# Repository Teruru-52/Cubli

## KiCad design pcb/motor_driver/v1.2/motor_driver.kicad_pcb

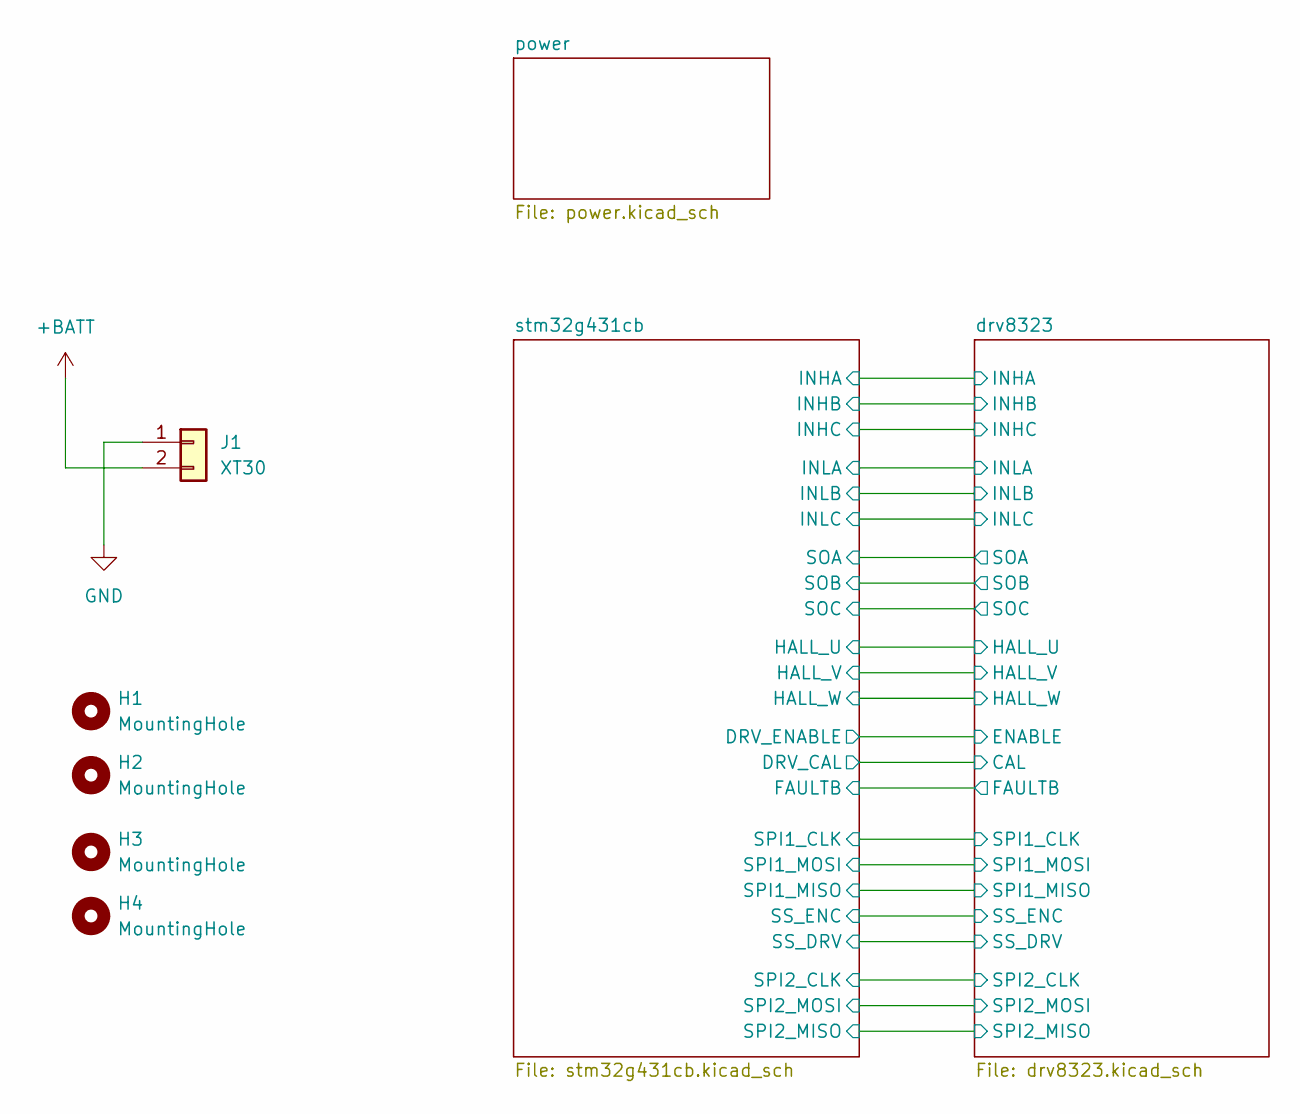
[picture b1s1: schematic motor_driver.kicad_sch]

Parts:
H1, H2, H3, H4: MountingHole; MountingHole_3.2mm_M3_Pad_TopBottom
J1: XT30; AMASS_XT30U-F_1x02_P5.0mm_Vertical

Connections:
+BATT: J1.2; also elsewhere on the board
GND: J1.1; also elsewhere on the board

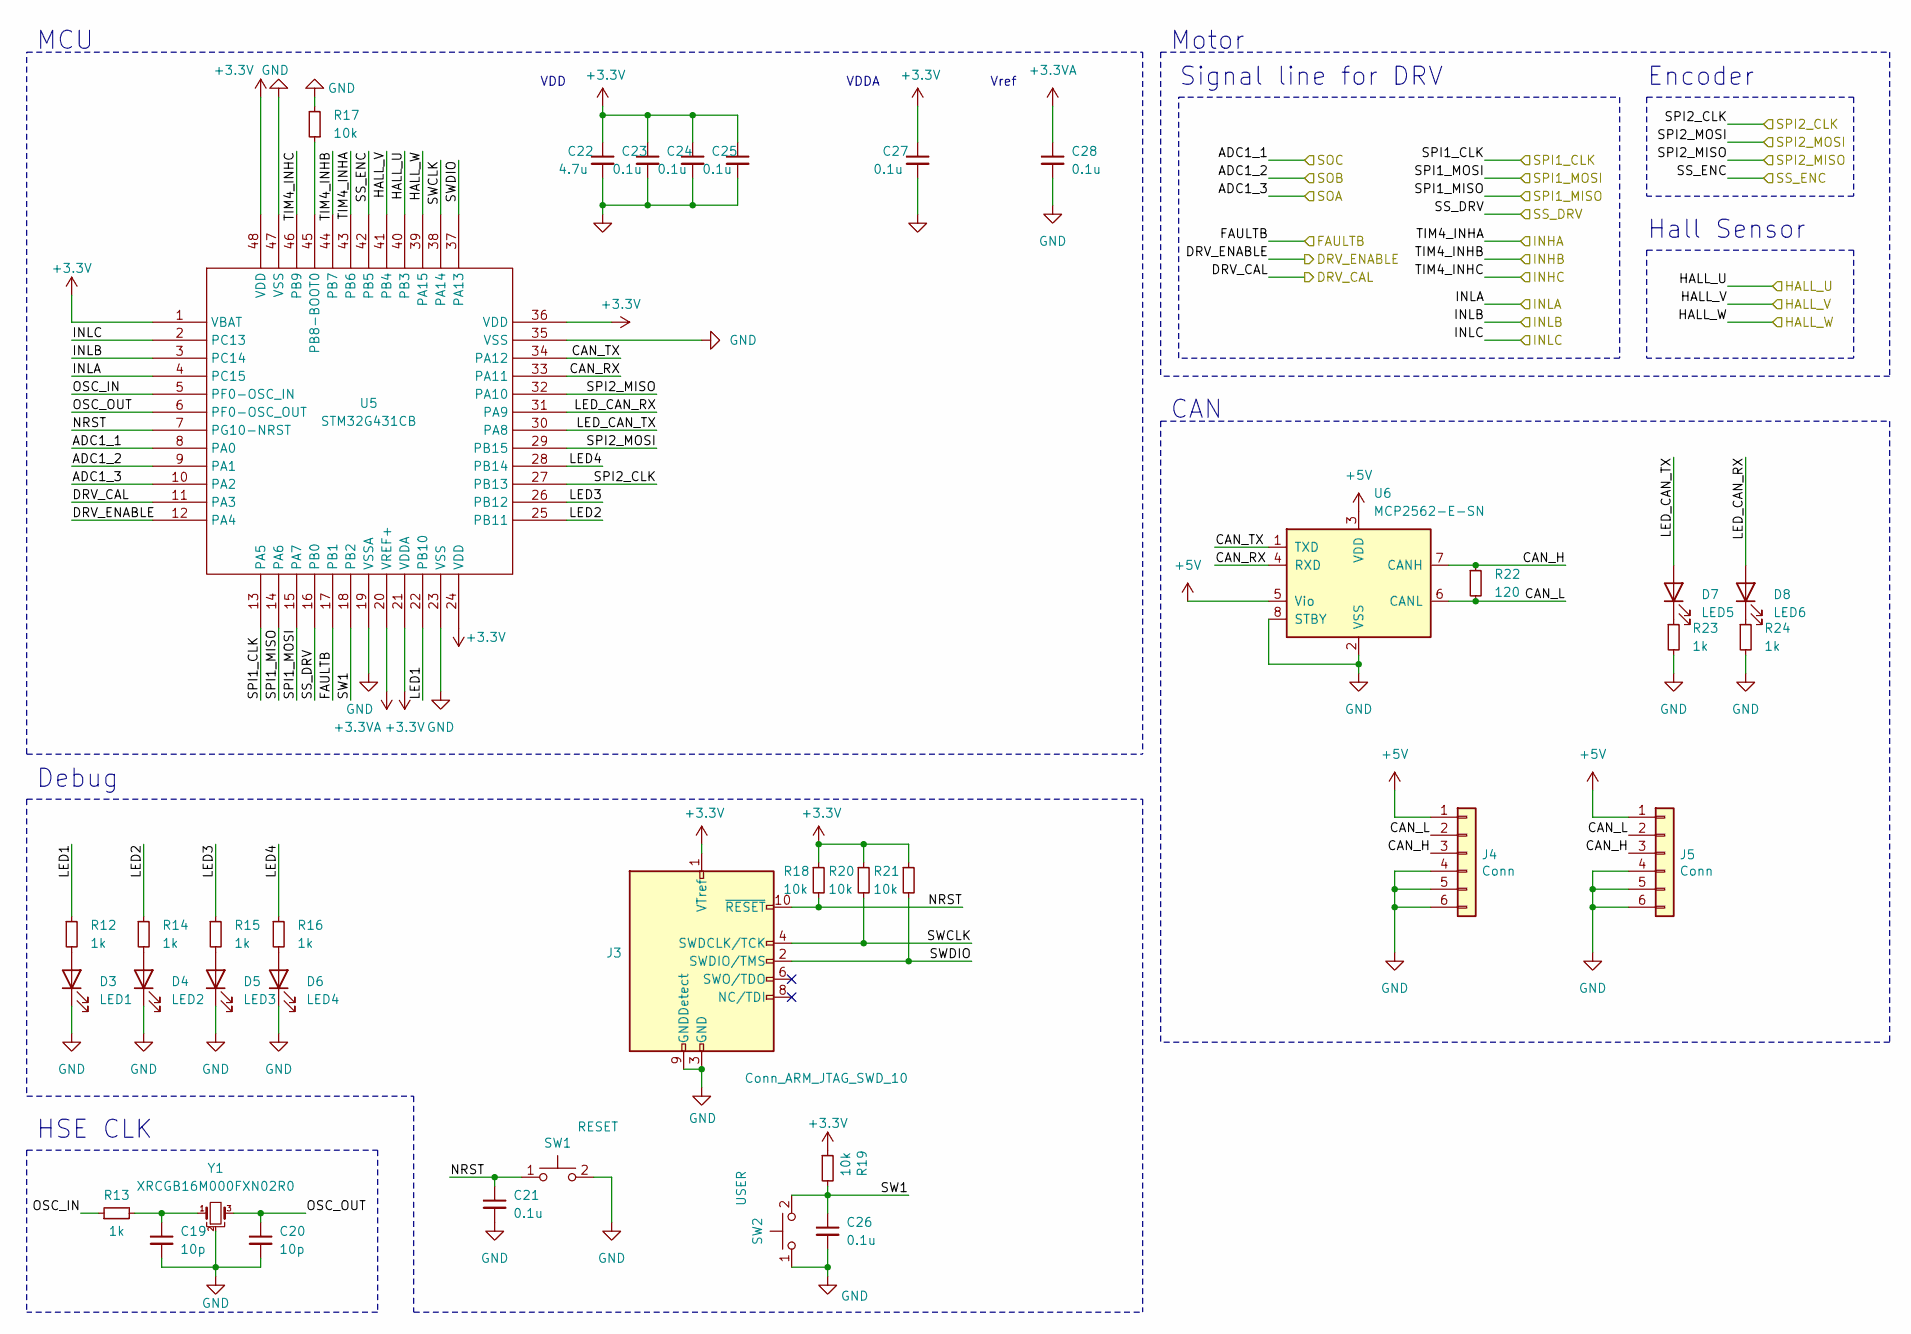
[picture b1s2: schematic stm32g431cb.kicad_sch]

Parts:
C19, C20: 10p; C_0402_1005Metric_Pad0.74x0.62mm_HandSolder
C21, C26: 0.1u; C_0603_1608Metric_Pad1.08x0.95mm_HandSolder
C22: 4.7u; C_0603_1608Metric
C23, C24, C25, C27, C28: 0.1u; C_0603_1608Metric
D3: LED1; LED_0603_1608Metric
D4: LED2; LED_0603_1608Metric
D5: LED3; LED_0603_1608Metric
D6: LED4; LED_0603_1608Metric
D7: LED5; LED_0603_1608Metric
D8: LED6; LED_0603_1608Metric
J3: Conn_ARM_JTAG_SWD_10; 322110010000
J4, J5: Conn; 21322604YY
R12, R14, R15, R16, R23, R24: 1k; R_0603_1608Metric_Pad0.98x0.95mm_HandSolder
R13: 1k; R_0402_1005Metric_Pad0.72x0.64mm_HandSolder
R17, R18, R19, R20, R21: 10k; R_0603_1608Metric_Pad0.98x0.95mm_HandSolder
R22: 120; R_0603_1608Metric_Pad0.98x0.95mm_HandSolder
SW1: RESET; TVAF06-A020B-R
SW2: USER; TVAF06-A020B-R
U5: STM32G431CB; LQFP-48_7x7mm_P0.5mm
U6: MCP2562-E-SN; SOIC-8_3.9x4.9mm_P1.27mm
Y1: XRCGB16M000FXN02R0

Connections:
+3.3V: C22.1, C23.1, C24.1, C25.1, C27.1, J3.1 (VTref), R18.1, R19.1, R20.1, R21.1, U5.1 (VBAT), U5.21 (VDDA), U5.24 (VDD), U5.36 (VDD), U5.48 (VDD); also elsewhere on the board
+3.3VA: C28.1, U5.20 (VREF+); also elsewhere on the board
+5V: J4.1, J5.1, U6.3 (VDD), U6.5 (Vio); also elsewhere on the board
/drv8323/HALL_U: U5.40 (PB3); also elsewhere on the board
/drv8323/HALL_V: U5.41 (PB4); also elsewhere on the board
/drv8323/HALL_W: U5.39 (PA15); also elsewhere on the board
/drv8323/SPI1_CLK: U5.13 (PA5); also elsewhere on the board
/drv8323/SPI1_MISO: U5.14 (PA6); also elsewhere on the board
/drv8323/SPI1_MOSI: U5.15 (PA7); also elsewhere on the board
/drv8323/SPI2_CLK: U5.27 (PB13); also elsewhere on the board
/drv8323/SPI2_MISO: U5.32 (PA10); also elsewhere on the board
/drv8323/SPI2_MOSI: U5.29 (PB15); also elsewhere on the board
/drv8323/SS_ENC: U5.42 (PB5); also elsewhere on the board
/stm32g431cb/ADC1_1: U5.8 (PA0); also elsewhere on the board
/stm32g431cb/ADC1_2: U5.9 (PA1); also elsewhere on the board
/stm32g431cb/ADC1_3: U5.10 (PA2); also elsewhere on the board
/stm32g431cb/CAN_H: J4.3, J5.3, R22.1, U6.7 (CANH)
/stm32g431cb/CAN_L: J4.2, J5.2, R22.2, U6.6 (CANL)
/stm32g431cb/CAN_RX: U5.33 (PA11), U6.4 (RXD)
/stm32g431cb/CAN_TX: U5.34 (PA12), U6.1 (TXD)
/stm32g431cb/DRV_CAL: U5.11 (PA3); also elsewhere on the board
/stm32g431cb/DRV_ENABLE: U5.12 (PA4); also elsewhere on the board
/stm32g431cb/FAULTB: U5.17 (PB1); also elsewhere on the board
/stm32g431cb/INLA: U5.4 (PC15); also elsewhere on the board
/stm32g431cb/INLB: U5.3 (PC14); also elsewhere on the board
/stm32g431cb/INLC: U5.2 (PC13); also elsewhere on the board
/stm32g431cb/LED1: R12.1, U5.22 (PB10)
/stm32g431cb/LED2: R14.1, U5.25 (PB11)
/stm32g431cb/LED3: R15.1, U5.26 (PB12)
/stm32g431cb/LED4: R16.1, U5.28 (PB14)
/stm32g431cb/LED_CAN_RX: D8.2 (A), U5.31 (PA9)
/stm32g431cb/LED_CAN_TX: D7.2 (A), U5.30 (PA8)
/stm32g431cb/NRST: C21.1, J3.10 (~RESET), R18.2, SW1.1, U5.7 (PG10-NRST)
/stm32g431cb/OSC_IN: R13.1, U5.5 (PF0-OSC_IN)
/stm32g431cb/OSC_OUT: C20.1, U5.6 (PF0-OSC_OUT), Y1.3
/stm32g431cb/SS_DRV: U5.16 (PB0); also elsewhere on the board
/stm32g431cb/SW1: C26.1, R19.2, SW2.2, U5.18 (PB2)
/stm32g431cb/SWCLK: J3.4 (SWDCLK/TCK), R20.2, U5.38 (PA14)
/stm32g431cb/SWDIO: J3.2 (SWDIO/TMS), R21.2, U5.37 (PA13)
/stm32g431cb/TIM4_INHA: U5.43 (PB6); also elsewhere on the board
/stm32g431cb/TIM4_INHB: U5.44 (PB7); also elsewhere on the board
/stm32g431cb/TIM4_INHC: U5.46 (PB9); also elsewhere on the board
GND: C19.2, C20.2, C21.2, C22.2, C23.2, C24.2, C25.2, C26.2, C27.2, C28.2, D3.1 (K), D4.1 (K), D5.1 (K), D6.1 (K), J3.3 (GND), J3.5 (GND), J3.9 (GNDDetect), J4.4, J4.5, J4.6, J5.4, J5.5, J5.6, R17.2, R23.2, R24.2, SW1.2, SW2.1, U5.19 (VSSA), U5.23 (VSS), U5.35 (VSS), U5.47 (VSS), U6.2 (VSS), U6.8 (STBY), Y1.2; also elsewhere on the board
unnamed: C19.1, R13.2, Y1.1
unnamed: D3.2 (A), R12.2
unnamed: D4.2 (A), R14.2
unnamed: D5.2 (A), R15.2
unnamed: D6.2 (A), R16.2
unnamed: D7.1 (K), R23.1
unnamed: D8.1 (K), R24.1
unnamed: R17.1, U5.45 (PB8-BOOT0)

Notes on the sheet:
Motor
HSE CLK
MCU
CAN
Encoder
Signal line for DRV
Debug
VDD
Vref
VDDA
Hall Sensor

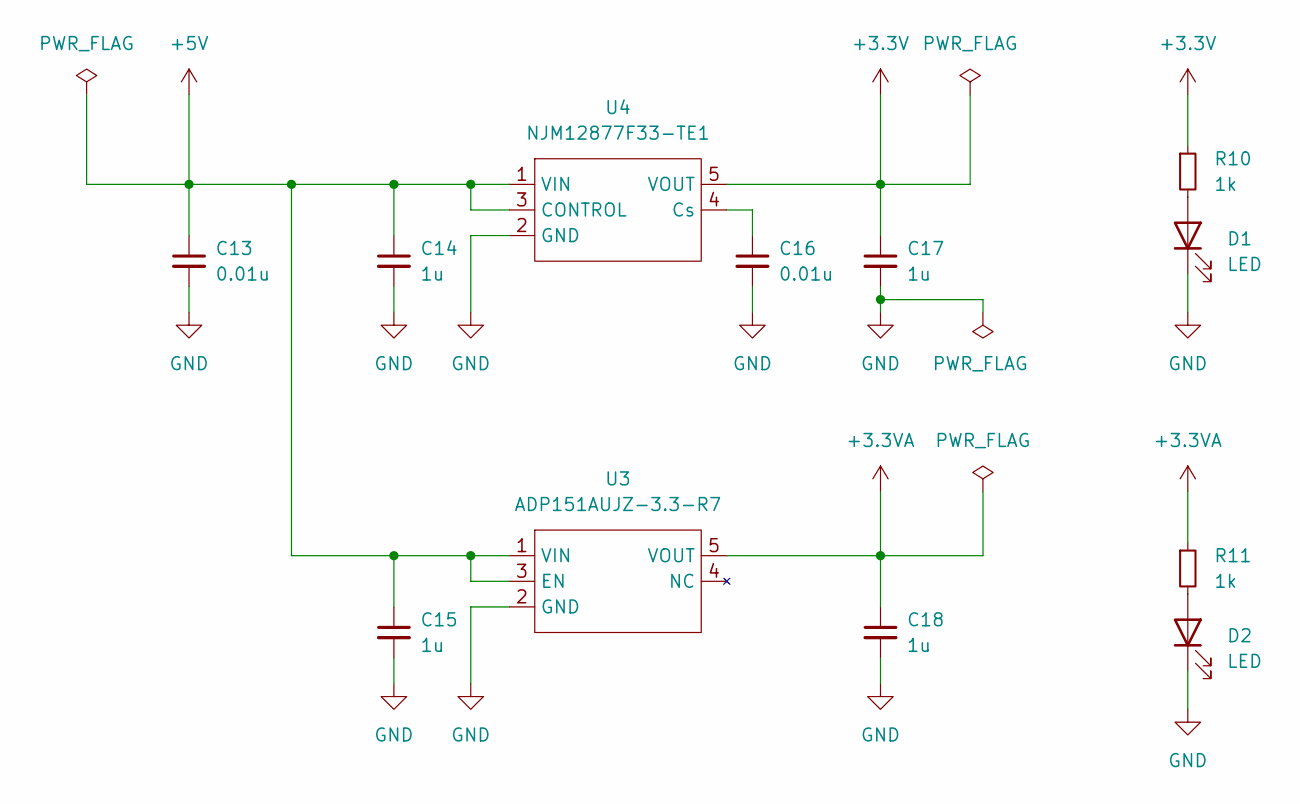
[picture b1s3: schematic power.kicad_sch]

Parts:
C13, C16: 0.01u; C_0603_1608Metric_Pad1.08x0.95mm_HandSolder
C14, C15, C17, C18: 1u; C_0603_1608Metric_Pad1.08x0.95mm_HandSolder
D1, D2: LED; LED_0603_1608Metric
R10, R11: 1k; R_0603_1608Metric_Pad0.98x0.95mm_HandSolder
U3: ADP151AUJZ-3.3-R7; SOT-23-5_HandSoldering
U4: NJM12877F33-TE1; SOT-23-5_HandSoldering

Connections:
+3.3V: C17.1, R10.1, U4.5 (VOUT); also elsewhere on the board
+3.3VA: C18.1, R11.1, U3.5 (VOUT); also elsewhere on the board
+5V: C13.1, C14.1, C15.1, U3.1 (VIN), U3.3 (EN), U4.1 (VIN), U4.3 (CONTROL); also elsewhere on the board
GND: C13.2, C14.2, C15.2, C16.2, C17.2, C18.2, D1.1 (K), D2.1 (K), U3.2 (GND), U4.2 (GND); also elsewhere on the board
unnamed: D1.2 (A), R10.2
unnamed: D2.2 (A), R11.2
unnamed: C16.1, U4.4 (Cs)

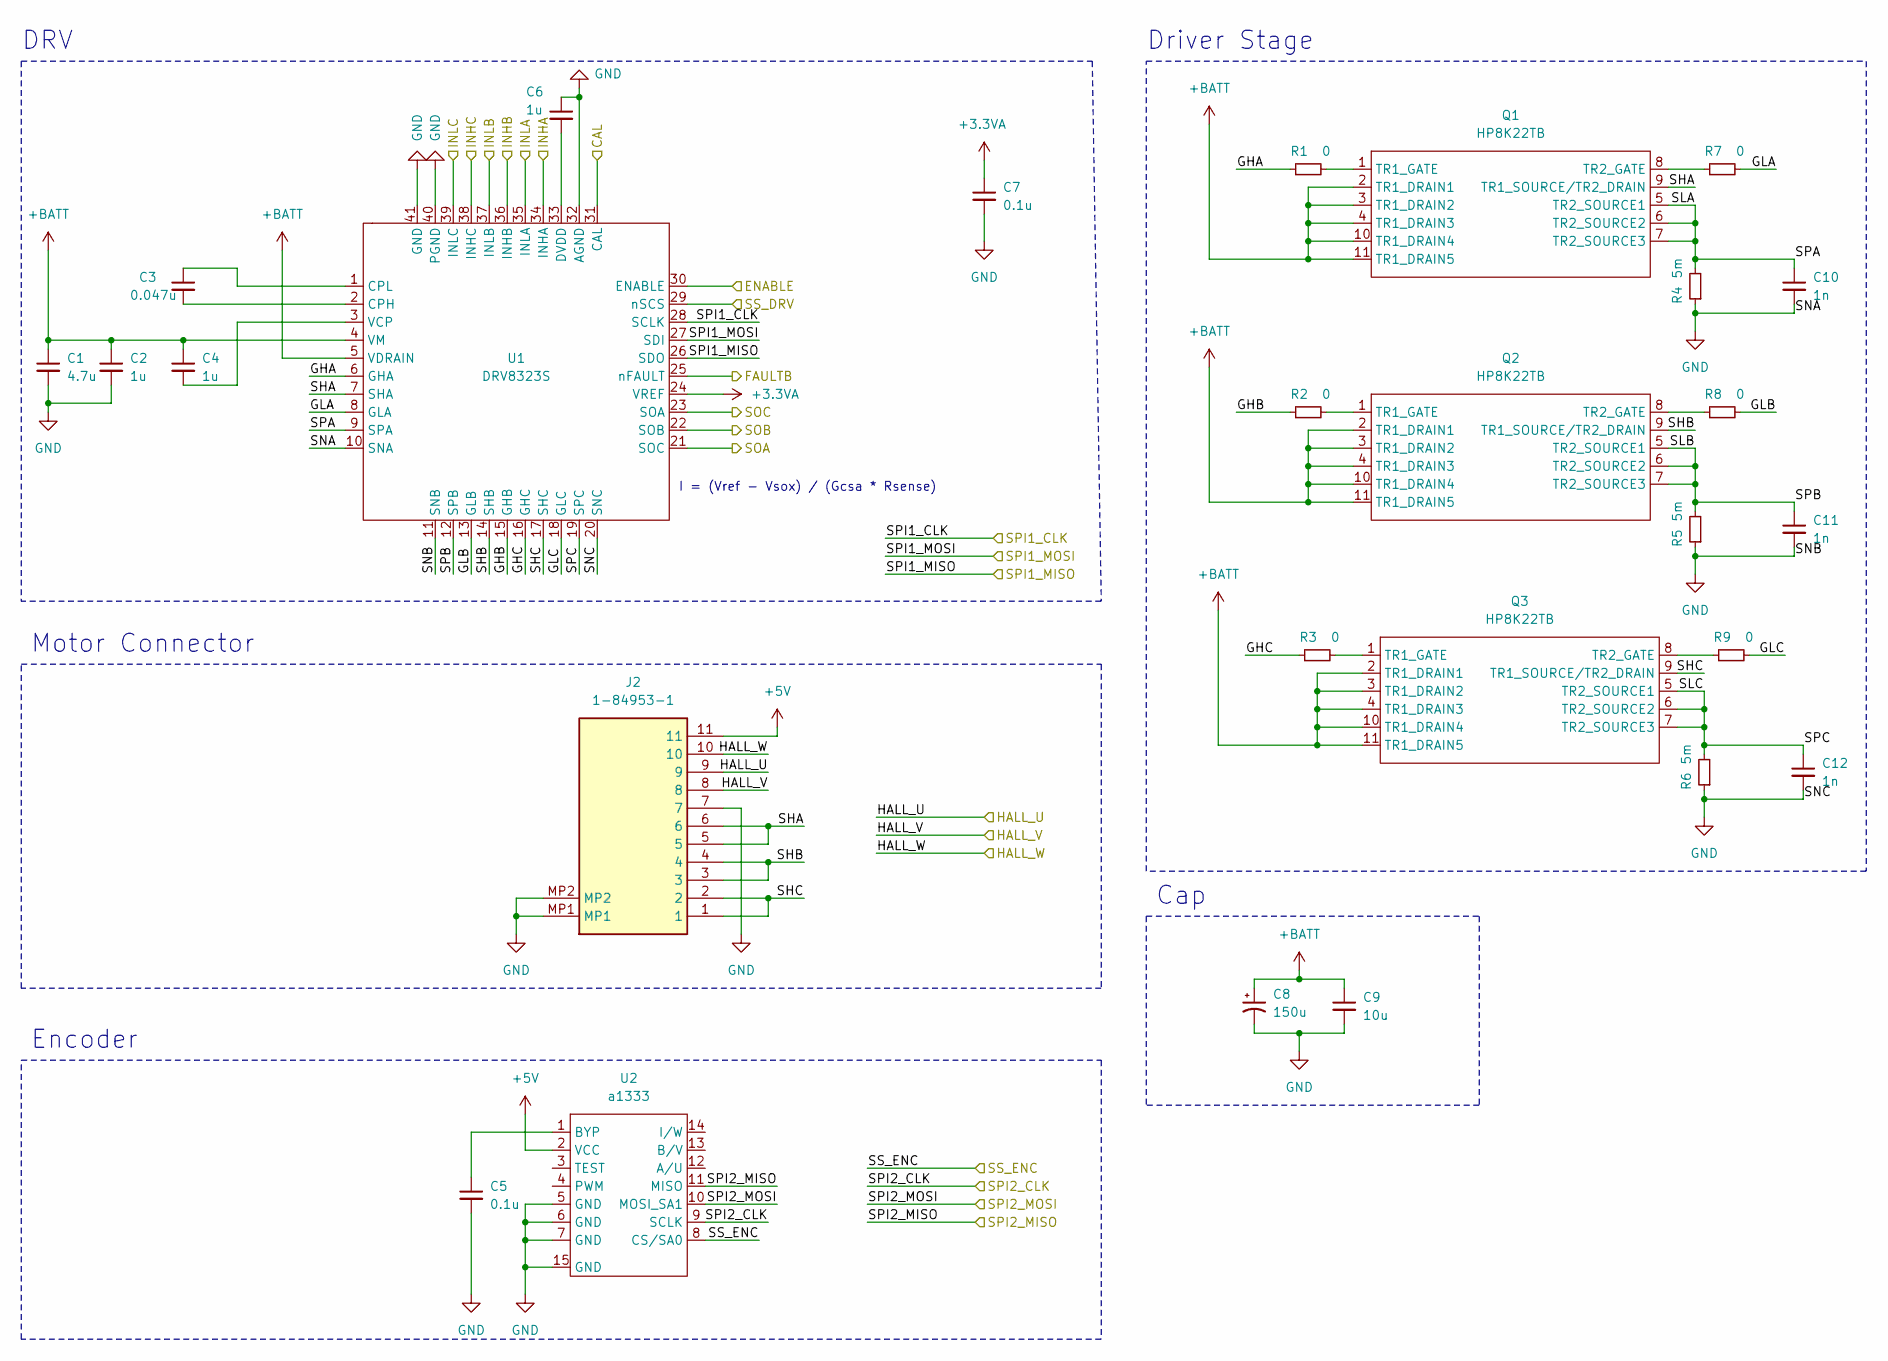
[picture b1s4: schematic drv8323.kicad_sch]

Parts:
C1: 4.7u; C_0603_1608Metric_Pad1.08x0.95mm_HandSolder
C2, C4, C6: 1u; C_0603_1608Metric_Pad1.08x0.95mm_HandSolder
C3: 0.047u; C_0603_1608Metric_Pad1.08x0.95mm_HandSolder
C5: 0.1u; C_0603_1608Metric_Pad1.08x0.95mm_HandSolder
C7: 0.1u; C_0402_1005Metric_Pad0.74x0.62mm_HandSolder
C8: 150u; CP_Elec_6.3x3.9
C9: 10u; C_0603_1608Metric_Pad1.08x0.95mm_HandSolder
C10, C11, C12: 1n; C_0402_1005Metric_Pad0.74x0.62mm_HandSolder
J2: 1-84953-1; Manufacturer_Part_Number 1-84953-1; Mouser Part Number 571-1-84953-1
Q1, Q2, Q3: HP8K22TB; HP8K24TB
R1, R2, R3, R7, R8, R9: 0; R_0805_2012Metric_Pad1.20x1.40mm_HandSolder
R4, R5, R6: 5m; R_2010_5025Metric_Pad1.40x2.65mm_HandSolder
U1: DRV8323S; QFN-40-1EP_6x6mm_P0.5mm_EP4.6x4.6mm
U2: a1333; HTSSOP-14-1EP_4.4x5mm_P0.65mm_EP3.4x5mm_Mask3x3.1mm

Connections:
+3.3VA: C7.1, U1.24 (VREF); also elsewhere on the board
+5V: J2.11, U2.2 (VCC); also elsewhere on the board
+BATT: C1.1, C2.1, C4.1, C8.1, C9.1, Q1.2 (TR1_DRAIN1), Q1.3 (TR1_DRAIN2), Q1.4 (TR1_DRAIN3), Q1.10 (TR1_DRAIN4), Q1.11 (TR1_DRAIN5), Q2.2 (TR1_DRAIN1), Q2.3 (TR1_DRAIN2), Q2.4 (TR1_DRAIN3), Q2.10 (TR1_DRAIN4), Q2.11 (TR1_DRAIN5), Q3.2 (TR1_DRAIN1), Q3.3 (TR1_DRAIN2), Q3.4 (TR1_DRAIN3), Q3.10 (TR1_DRAIN4), Q3.11 (TR1_DRAIN5), U1.4 (VM), U1.5 (VDRAIN); also elsewhere on the board
/drv8323/GHA: R1.1, U1.6 (GHA)
/drv8323/GHB: R2.1, U1.15 (GHB)
/drv8323/GHC: R3.1, U1.16 (GHC)
/drv8323/GLA: R7.2, U1.8 (GLA)
/drv8323/GLB: R8.2, U1.13 (GLB)
/drv8323/GLC: R9.2, U1.18 (GLC)
/drv8323/HALL_U: J2.9; also elsewhere on the board
/drv8323/HALL_V: J2.8; also elsewhere on the board
/drv8323/HALL_W: J2.10; also elsewhere on the board
/drv8323/SHA: J2.5, J2.6, Q1.9 (TR1_SOURCE/TR2_DRAIN), U1.7 (SHA)
/drv8323/SHB: J2.3, J2.4, Q2.9 (TR1_SOURCE/TR2_DRAIN), U1.14 (SHB)
/drv8323/SHC: J2.1, J2.2, Q3.9 (TR1_SOURCE/TR2_DRAIN), U1.17 (SHC)
/drv8323/SLA: C10.1, Q1.5 (TR2_SOURCE1), Q1.6 (TR2_SOURCE2), Q1.7 (TR2_SOURCE3), R4.2, U1.9 (SPA)
/drv8323/SLB: C11.1, Q2.5 (TR2_SOURCE1), Q2.6 (TR2_SOURCE2), Q2.7 (TR2_SOURCE3), R5.2, U1.12 (SPB)
/drv8323/SLC: C12.1, Q3.5 (TR2_SOURCE1), Q3.6 (TR2_SOURCE2), Q3.7 (TR2_SOURCE3), R6.2, U1.19 (SPC)
/drv8323/SPI1_CLK: U1.28 (SCLK); also elsewhere on the board
/drv8323/SPI1_MISO: U1.26 (SDO); also elsewhere on the board
/drv8323/SPI1_MOSI: U1.27 (SDI); also elsewhere on the board
/drv8323/SPI2_CLK: U2.9 (SCLK); also elsewhere on the board
/drv8323/SPI2_MISO: U2.11 (MISO); also elsewhere on the board
/drv8323/SPI2_MOSI: U2.10 (MOSI_SA1); also elsewhere on the board
/drv8323/SS_ENC: U2.8 (CS/SA0); also elsewhere on the board
/stm32g431cb/ADC1_1: U1.23 (SOA); also elsewhere on the board
/stm32g431cb/ADC1_2: U1.22 (SOB); also elsewhere on the board
/stm32g431cb/ADC1_3: U1.21 (SOC); also elsewhere on the board
/stm32g431cb/DRV_CAL: U1.31 (CAL); also elsewhere on the board
/stm32g431cb/DRV_ENABLE: U1.30 (ENABLE); also elsewhere on the board
/stm32g431cb/FAULTB: U1.25 (nFAULT); also elsewhere on the board
/stm32g431cb/INLA: U1.35 (INLA); also elsewhere on the board
/stm32g431cb/INLB: U1.37 (INLB); also elsewhere on the board
/stm32g431cb/INLC: U1.39 (INLC); also elsewhere on the board
/stm32g431cb/SS_DRV: U1.29 (nSCS); also elsewhere on the board
/stm32g431cb/TIM4_INHA: U1.34 (INHA); also elsewhere on the board
/stm32g431cb/TIM4_INHB: U1.36 (INHB); also elsewhere on the board
/stm32g431cb/TIM4_INHC: U1.38 (INHC); also elsewhere on the board
GND: C1.2, C2.2, C5.2, C6.1, C7.2, C8.2, C9.2, C10.2, C11.2, C12.2, J2.7, J2.MP1, J2.MP2, R4.1, R5.1, R6.1, U1.10 (SNA), U1.11 (SNB), U1.20 (SNC), U1.32 (AGND), U1.40 (PGND), U1.41 (GND), U2.5 (GND), U2.6 (GND), U2.7 (GND), U2.15 (GND); also elsewhere on the board
unnamed: Q1.1 (TR1_GATE), R1.2
unnamed: Q1.8 (TR2_GATE), R7.1
unnamed: Q2.1 (TR1_GATE), R2.2
unnamed: Q2.8 (TR2_GATE), R8.1
unnamed: Q3.1 (TR1_GATE), R3.2
unnamed: Q3.8 (TR2_GATE), R9.1
unnamed: C3.2, U1.2 (CPH)
unnamed: C3.1, U1.1 (CPL)
unnamed: C6.2, U1.33 (DVDD)
unnamed: C4.2, U1.3 (VCP)
unnamed: C5.1, U2.1 (BYP)

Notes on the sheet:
Driver Stage
DRV
Motor Connector
Cap
Encoder
I = (Vref - Vsox) / (Gcsa * Rsense)

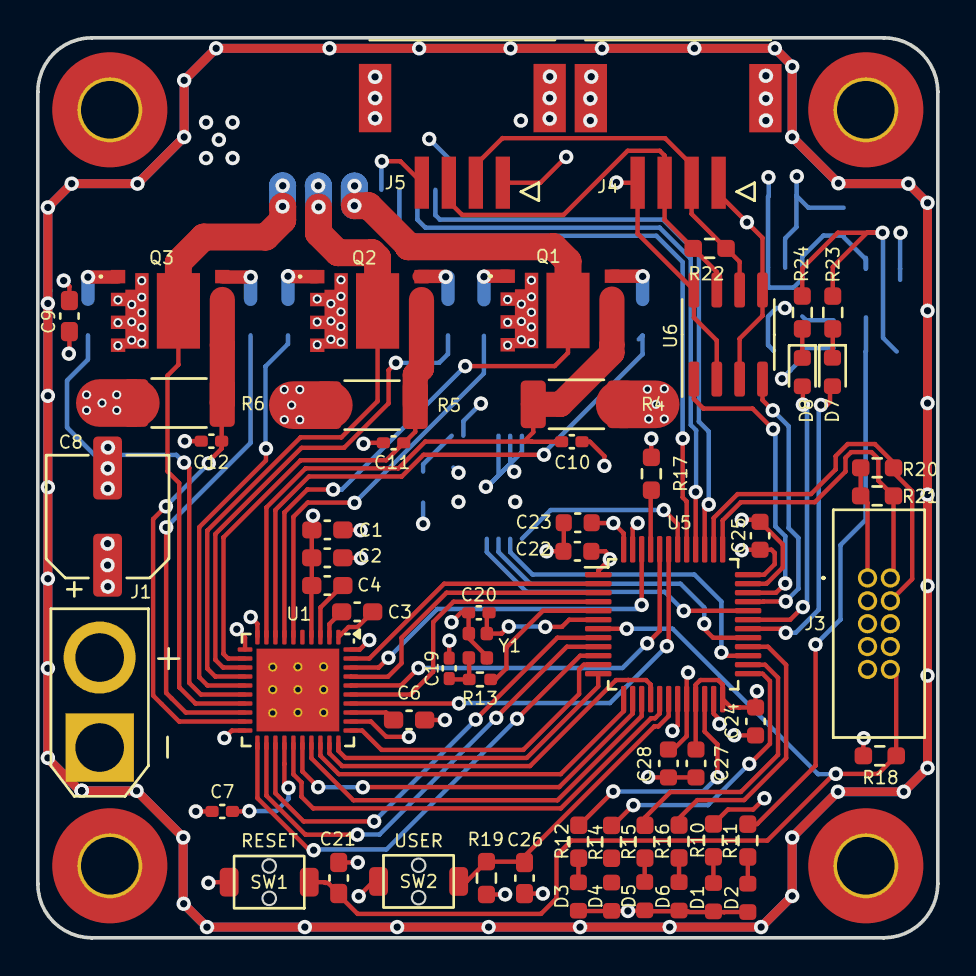
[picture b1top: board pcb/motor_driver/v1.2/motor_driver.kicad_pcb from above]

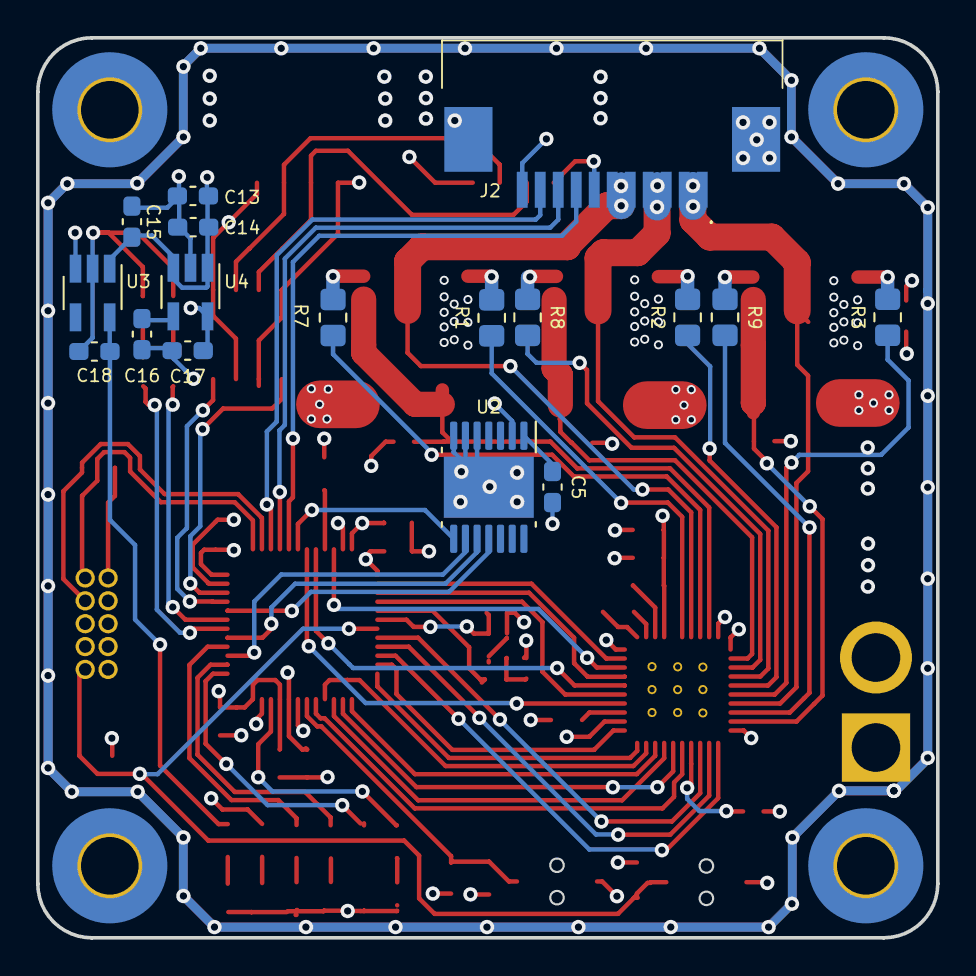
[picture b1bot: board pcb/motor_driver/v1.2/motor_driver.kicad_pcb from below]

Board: 4 copper layers, 50.0 x 50.0 mm, 81 parts (17 on the bottom side), 78 nets.

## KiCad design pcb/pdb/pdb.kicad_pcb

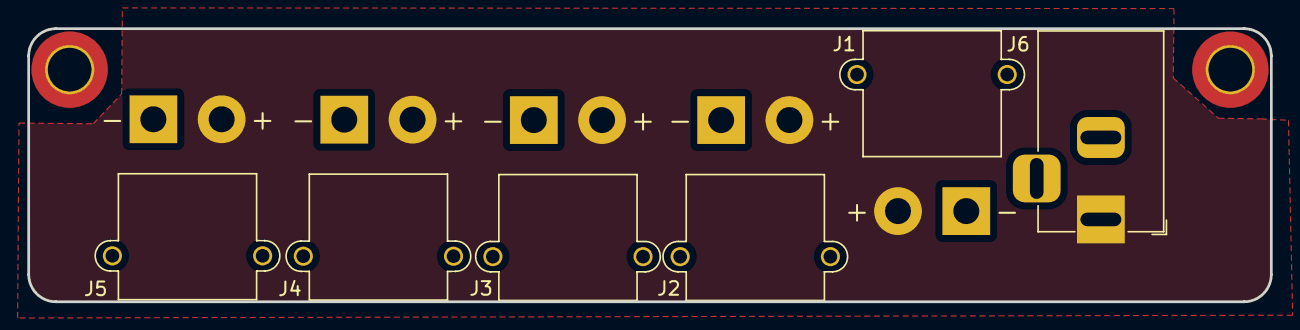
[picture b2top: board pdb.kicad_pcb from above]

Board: 2 copper layers, 91.0 x 20.0 mm, 8 parts (0 on the bottom side), 2 nets, no tracks yet.

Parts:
H1, H2: MountingHole; MountingHole_3.2mm_M3_Pad_TopBottom
J1, J2, J3, J4, J5: Conn_01x02; AMASS_XT30PW-M_1x02_P2.50mm_Horizontal
J6: Jack-DC; BarrelJack_Horizontal

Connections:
+BATT: J1.2, J2.2, J3.2, J4.2, J5.2, J6.1
GND: J1.1, J2.1, J3.1, J4.1, J5.1, J6.2

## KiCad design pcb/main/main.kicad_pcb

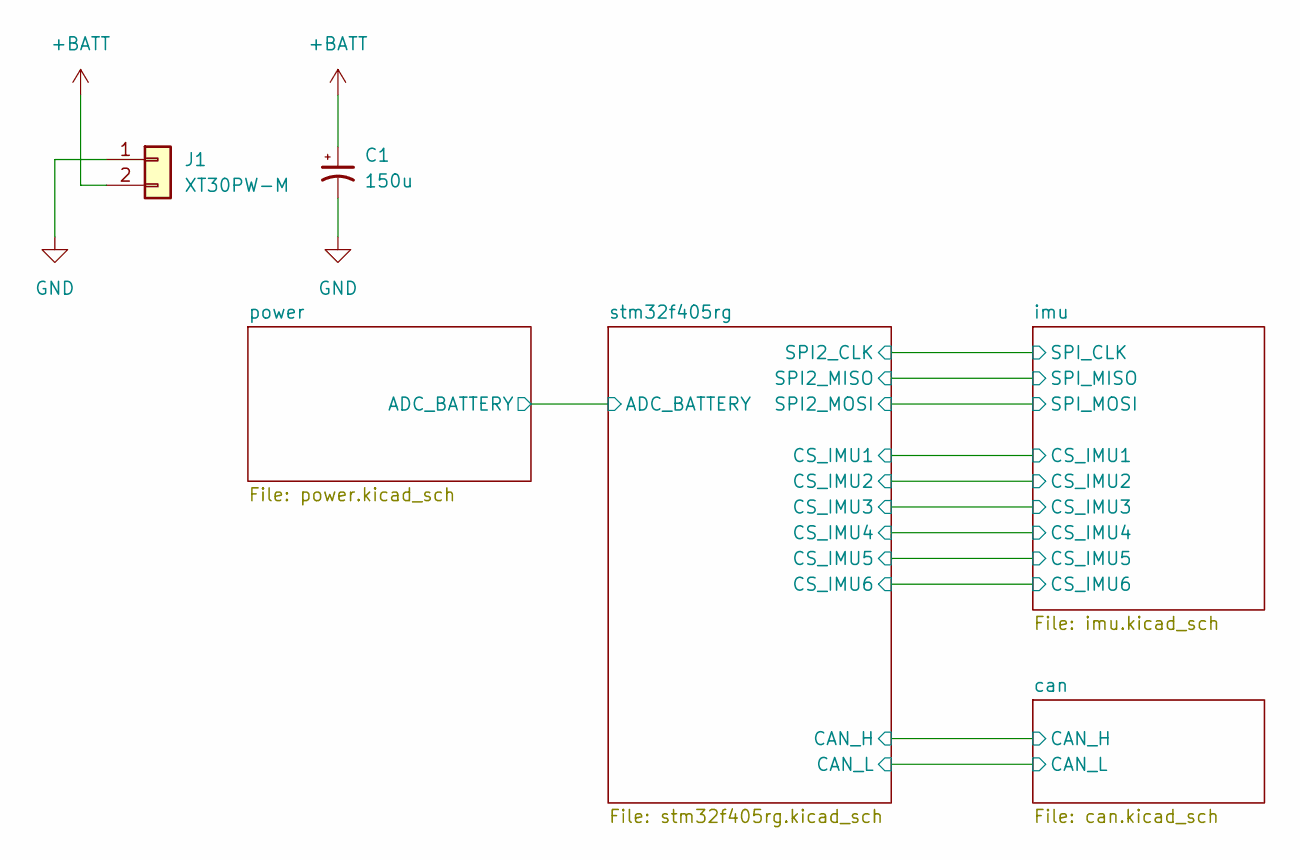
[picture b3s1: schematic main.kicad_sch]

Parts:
C1: 150u; CP_Elec_8x10.5
J1: XT30PW-M; AMASS_XT30PW-M_1x02_P2.50mm_Horizontal

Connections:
+BATT: C1.1, J1.2; also elsewhere on the board
GND: C1.2, J1.1; also elsewhere on the board

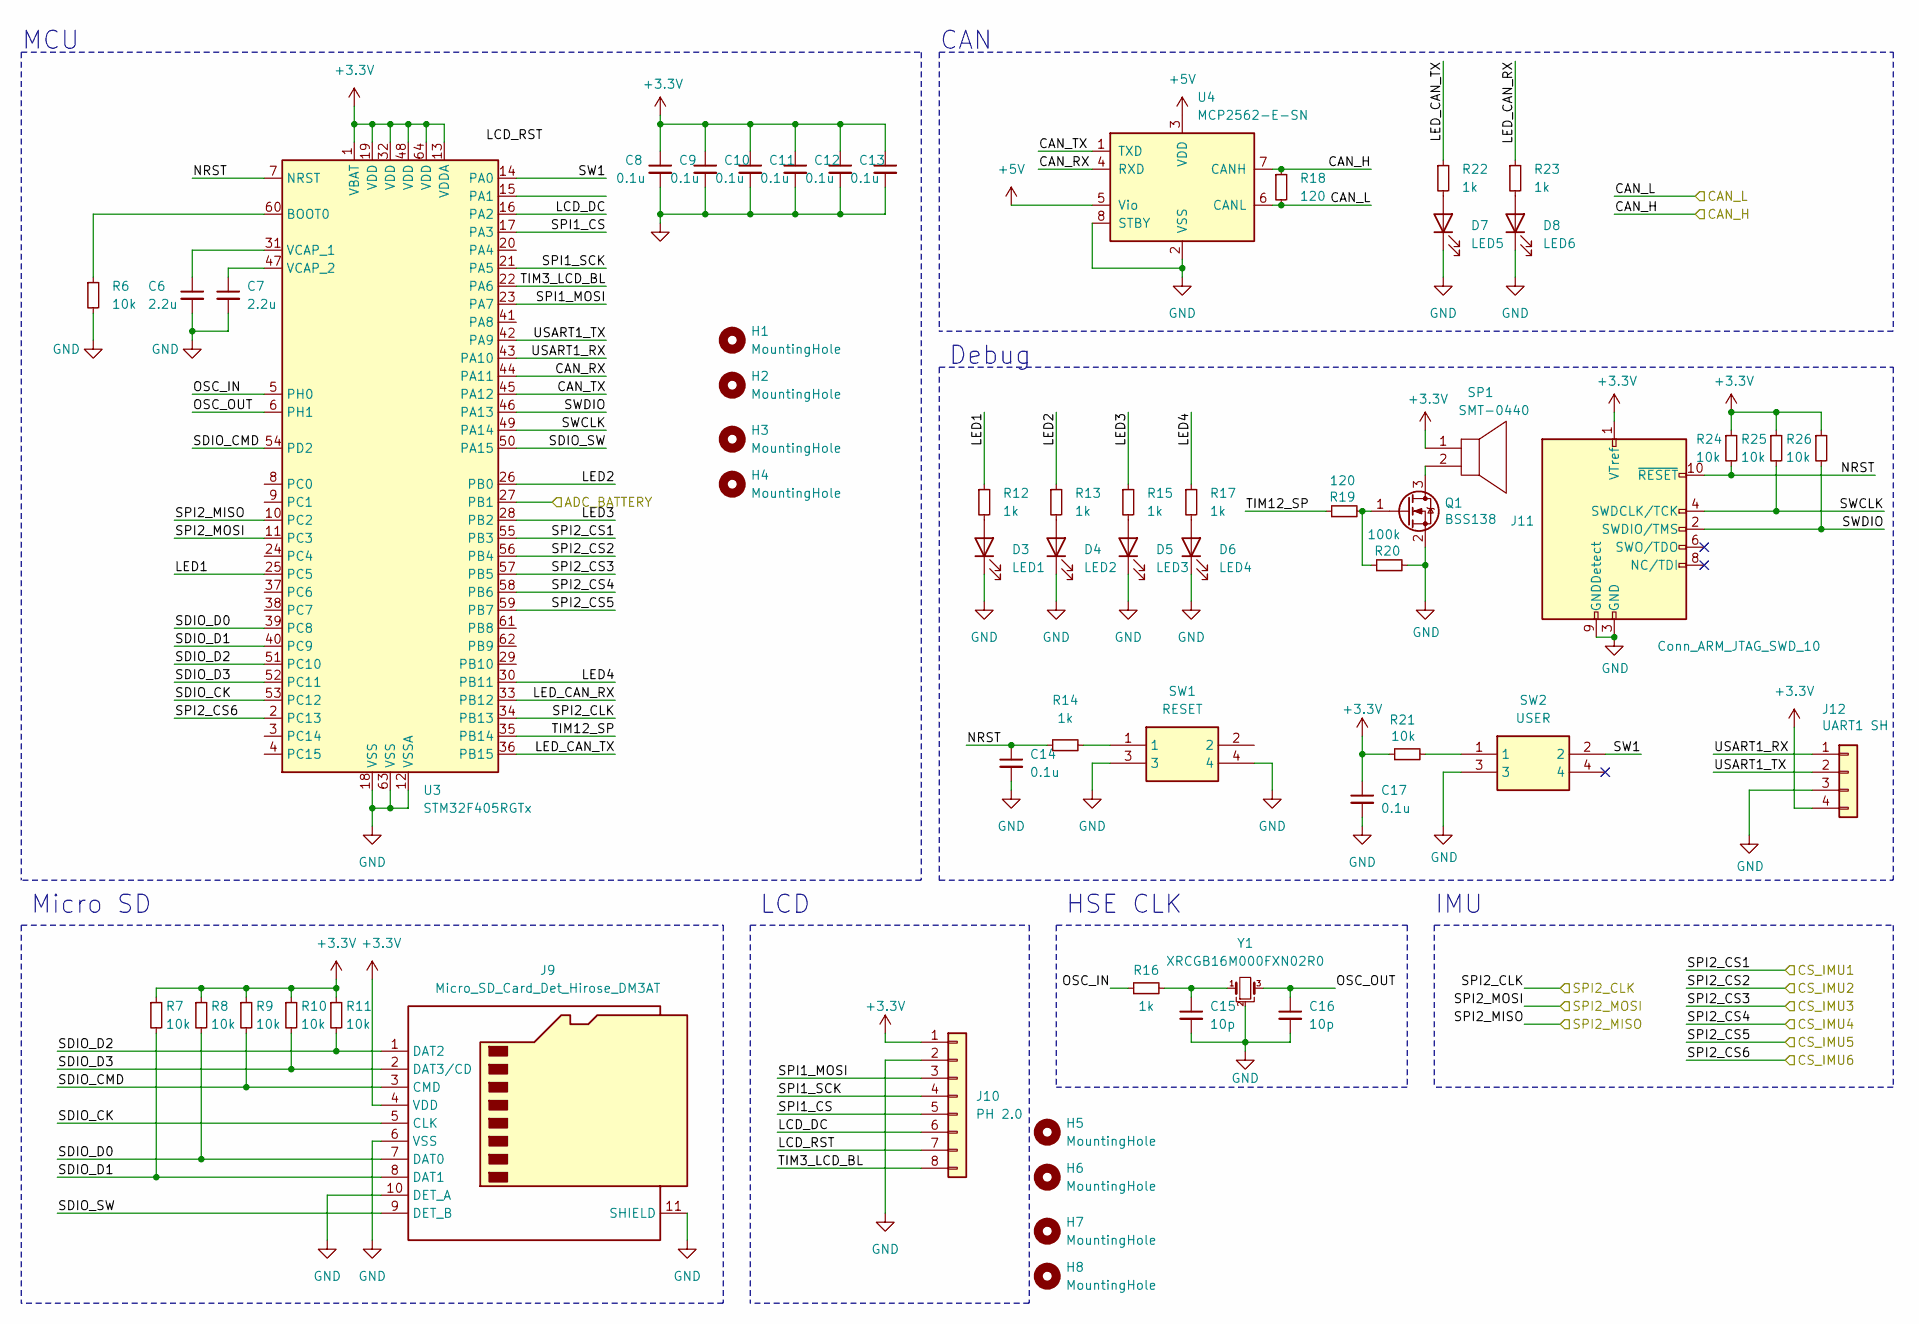
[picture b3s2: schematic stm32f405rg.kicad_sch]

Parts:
C6, C7: 2.2u; C_0603_1608Metric_Pad1.08x0.95mm_HandSolder
C8, C9, C10, C11, C12, C13, C14, C17: 0.1u; C_0603_1608Metric_Pad1.08x0.95mm_HandSolder
C15, C16: 10p; C_0402_1005Metric_Pad0.74x0.62mm_HandSolder
D3: LED1; LED_0603_1608Metric
D4: LED2; LED_0603_1608Metric
D5: LED3; LED_0603_1608Metric
D6: LED4; LED_0603_1608Metric
D7: LED5; LED_0603_1608Metric
D8: LED6; LED_0603_1608Metric
H1, H2, H3, H4: MountingHole; MountingHole_3.2mm_M3_Pad_TopBottom
H5, H6, H7, H8: MountingHole; MountingHole_2.2mm_M2_ISO14580_Pad
J9: Micro_SD_Card_Det_Hirose_DM3AT; microSD_HC_Hirose_DM3AT-SF-PEJM5
J10: PH 2.0; JST_PH_S8B-PH-SM4-TB_1x08-1MP_P2.00mm_Horizontal
J11: Conn_ARM_JTAG_SWD_10; 322110010000
J12: UART1 SH; PinHeader_1x04_P2.54mm_Vertical
Q1: BSS138; SOT-23
R6: 10k; R_0603_1608Metric
R7, R8, R9, R10, R11, R21, R24, R25, R26: 10k; R_0603_1608Metric_Pad0.98x0.95mm_HandSolder
R12, R13, R14, R15, R16, R17, R22, R23: 1k; R_0603_1608Metric_Pad0.98x0.95mm_HandSolder
R18, R19: 120; R_0603_1608Metric_Pad0.98x0.95mm_HandSolder
R20: 100k; R_0603_1608Metric_Pad0.98x0.95mm_HandSolder
SP1: SMT-0440; STM0440-T-R
SW1: RESET; TVAF06A020BR; Manufacturer_Part_Number SKRPACE010; Mouser Part Number 688-SKRPACE010
SW2: USER; TVAF06A020BR; Manufacturer_Part_Number SKRPACE010; Mouser Part Number 688-SKRPACE010
U3: STM32F405RGTx; LQFP-64_10x10mm_P0.5mm
U4: MCP2562-E-SN; SOIC-8_3.9x4.9mm_P1.27mm
Y1: XRCGB16M000FXN02R0

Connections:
+3.3V: C8.1, C9.1, C10.1, C11.1, C12.1, C13.1, C17.1, J9.4 (VDD), J10.1, J11.1 (VTref), J12.4, R7.1, R8.1, R9.1, R10.1, R11.1, R21.1, R24.1, R25.1, R26.1, SP1.1, U3.1 (VBAT), U3.13 (VDDA), U3.19 (VDD), U3.32 (VDD), U3.48 (VDD), U3.64 (VDD); also elsewhere on the board
+5V: U4.3 (VDD), U4.5 (Vio); also elsewhere on the board
/can/CAN_H: R18.1, U4.7 (CANH); also elsewhere on the board
/can/CAN_L: R18.2, U4.6 (CANL); also elsewhere on the board
/imu/SPI_CLK: U3.34 (PB13); also elsewhere on the board
/imu/SPI_MISO: U3.10 (PC2); also elsewhere on the board
/imu/SPI_MOSI: U3.11 (PC3); also elsewhere on the board
/power/ADC_BATTERY: U3.27 (PB1); also elsewhere on the board
/stm32f405rg/CAN_RX: U3.44 (PA11), U4.4 (RXD)
/stm32f405rg/CAN_TX: U3.45 (PA12), U4.1 (TXD)
/stm32f405rg/LCD_DC: J10.6, U3.16 (PA2)
/stm32f405rg/LCD_RST: J10.7
/stm32f405rg/LED1: R12.1, U3.25 (PC5)
/stm32f405rg/LED2: R13.1, U3.26 (PB0)
/stm32f405rg/LED3: R15.1, U3.28 (PB2)
/stm32f405rg/LED4: R17.1, U3.30 (PB11)
/stm32f405rg/LED_CAN_RX: R23.1, U3.33 (PB12)
/stm32f405rg/LED_CAN_TX: R22.1, U3.36 (PB15)
/stm32f405rg/NRST: C14.1, J11.10 (~RESET), R14.1, R24.2, U3.7 (NRST)
/stm32f405rg/OSC_IN: R16.1, U3.5 (PH0)
/stm32f405rg/OSC_OUT: C16.1, U3.6 (PH1), Y1.3
/stm32f405rg/SDIO_CK: J9.5 (CLK), U3.53 (PC12)
/stm32f405rg/SDIO_CMD: J9.3 (CMD), R9.2, U3.54 (PD2)
/stm32f405rg/SDIO_D0: J9.7 (DAT0), R8.2, U3.39 (PC8)
/stm32f405rg/SDIO_D1: J9.8 (DAT1), R7.2, U3.40 (PC9)
/stm32f405rg/SDIO_D2: J9.1 (DAT2), R11.2, U3.51 (PC10)
/stm32f405rg/SDIO_D3: J9.2 (DAT3/CD), R10.2, U3.52 (PC11)
/stm32f405rg/SDIO_SW: J9.9 (DET_B), U3.50 (PA15)
/stm32f405rg/SPI1_CS: J10.5, U3.17 (PA3)
/stm32f405rg/SPI1_MOSI: J10.3, U3.23 (PA7)
/stm32f405rg/SPI1_SCK: J10.4, U3.21 (PA5)
/stm32f405rg/SPI2_CS1: U3.55 (PB3); also elsewhere on the board
/stm32f405rg/SPI2_CS2: U3.56 (PB4); also elsewhere on the board
/stm32f405rg/SPI2_CS3: U3.57 (PB5); also elsewhere on the board
/stm32f405rg/SPI2_CS4: U3.58 (PB6); also elsewhere on the board
/stm32f405rg/SPI2_CS5: U3.59 (PB7); also elsewhere on the board
/stm32f405rg/SPI2_CS6: U3.2 (PC13); also elsewhere on the board
/stm32f405rg/SW1: SW2.2, U3.14 (PA0)
/stm32f405rg/SWCLK: J11.4 (SWDCLK/TCK), R25.2, U3.49 (PA14)
/stm32f405rg/SWDIO: J11.2 (SWDIO/TMS), R26.2, U3.46 (PA13)
/stm32f405rg/TIM3_LCD_BL: J10.8, U3.22 (PA6)
/stm32f405rg/TIM12_SP: R19.1, U3.35 (PB14)
/stm32f405rg/USART1_RX: J12.1, U3.43 (PA10)
/stm32f405rg/USART1_TX: J12.2, U3.42 (PA9)
GND: C6.2, C7.2, C8.2, C9.2, C10.2, C11.2, C12.2, C13.2, C14.2, C15.2, C16.2, C17.2, D3.1 (K), D4.1 (K), D5.1 (K), D6.1 (K), D7.1 (K), D8.1 (K), J9.6 (VSS), J9.10 (DET_A), J9.11 (SHIELD), J10.2, J11.3 (GND), J11.5 (GND), J11.9 (GNDDetect), J12.3, Q1.2 (S), R6.2, R20.2, SW1.3, SW1.4, SW2.3, U3.12 (VSSA), U3.18 (VSS), U3.63 (VSS), U4.2 (VSS), U4.8 (STBY), Y1.2; also elsewhere on the board
unnamed: C15.1, R16.2, Y1.1
unnamed: D3.2 (A), R12.2
unnamed: D4.2 (A), R13.2
unnamed: D5.2 (A), R15.2
unnamed: D6.2 (A), R17.2
unnamed: D7.2 (A), R22.2
unnamed: D8.2 (A), R23.2
unnamed: Q1.3 (D), SP1.2
unnamed: Q1.1 (G), R19.2, R20.1
unnamed: R14.2, SW1.1
unnamed: R21.2, SW2.1
unnamed: R6.1, U3.60 (BOOT0)
unnamed: C6.1, U3.31 (VCAP_1)
unnamed: C7.1, U3.47 (VCAP_2)

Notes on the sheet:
CAN
MCU
Micro SD
Debug
IMU
HSE CLK
LCD

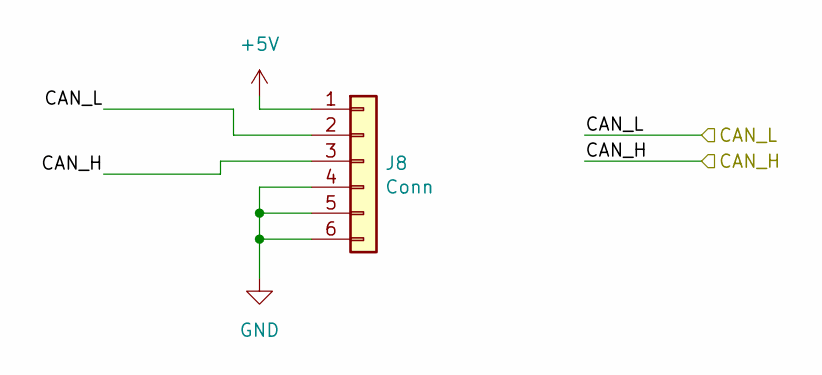
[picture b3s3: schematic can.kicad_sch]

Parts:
J8: Conn; 21322604YY

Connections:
+5V: J8.1; also elsewhere on the board
/can/CAN_H: J8.3; also elsewhere on the board
/can/CAN_L: J8.2; also elsewhere on the board
GND: J8.4, J8.5, J8.6; also elsewhere on the board
